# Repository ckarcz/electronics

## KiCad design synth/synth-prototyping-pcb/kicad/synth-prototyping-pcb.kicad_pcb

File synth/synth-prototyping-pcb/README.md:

# Prototyping PCB for Eurorack

Basic breadboard style pcb with Eurorack power connector.

# PCB

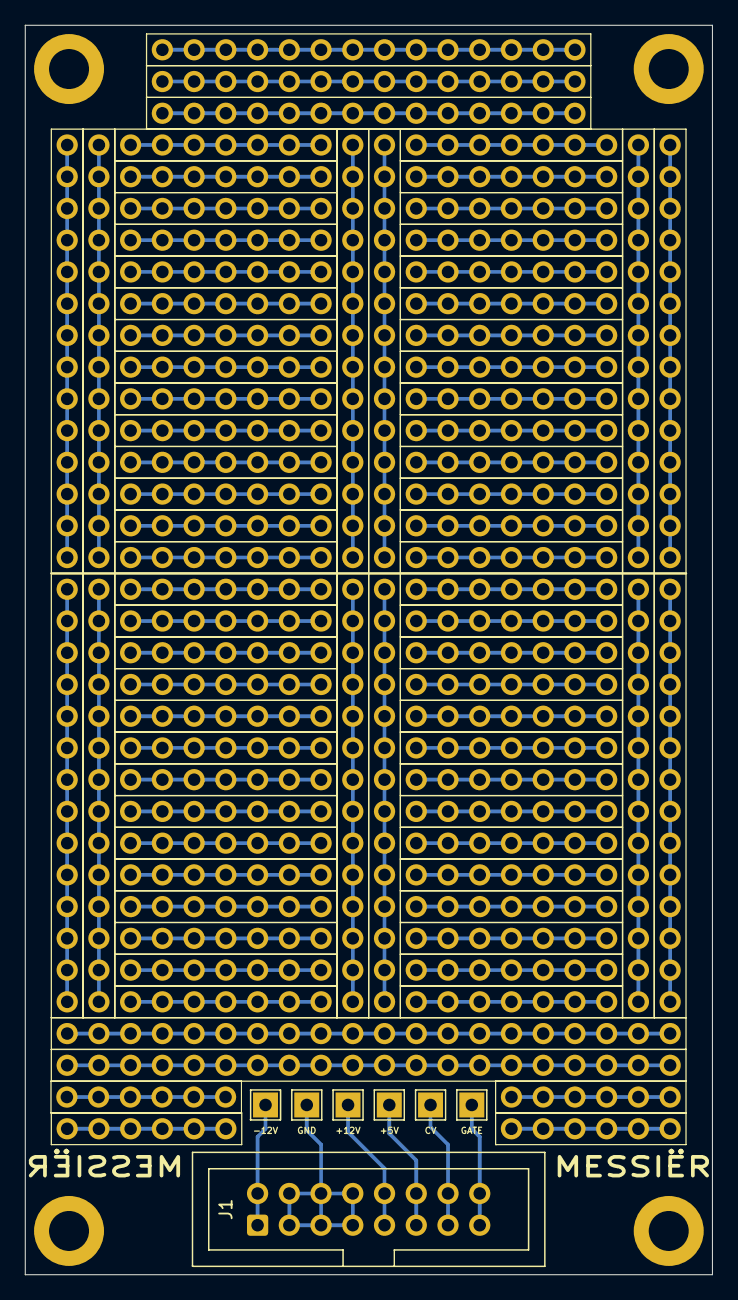
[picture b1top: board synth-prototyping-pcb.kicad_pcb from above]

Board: 2 copper layers, 55.0 x 100.0 mm, 11 parts (0 on the bottom side), 6 nets.

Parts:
J1: Conn_02x16_Odd_Even; IDC-Header_2x08_P2.54mm_Vertical
M1, M1#2, M1#3, M1#4: MountingHole_3.2mm_M3_DIN965_Pad
TP1: +5V; TestPoint_THTPad_2.0x2.0mm_Drill1.0mm
TP2: GND; TestPoint_THTPad_2.0x2.0mm_Drill1.0mm
TP3: +12V; TestPoint_THTPad_2.0x2.0mm_Drill1.0mm
TP4: -12V; TestPoint_THTPad_2.0x2.0mm_Drill1.0mm
TP5: CV; TestPoint_THTPad_2.0x2.0mm_Drill1.0mm
TP6: GATE; TestPoint_THTPad_2.0x2.0mm_Drill1.0mm

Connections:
+5V: J1.11, J1.12, TP1.1
+12V: J1.9, J1.10, TP3.1
-12V: J1.1, J1.2, TP4.1
CV: J1.13, J1.14, TP5.1
GATE: J1.15, J1.16, TP6.1
GND: J1.3, J1.4, J1.5, J1.6, J1.7, J1.8, TP2.1

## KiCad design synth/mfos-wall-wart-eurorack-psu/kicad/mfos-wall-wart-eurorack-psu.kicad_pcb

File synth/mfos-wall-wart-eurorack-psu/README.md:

# MFOS Wall Wart PSU For Eurorack

Basic wall wart design but with eurorack power rails + connector. Sub 100mm desing for cheap PCB manufactoring.

[Based on Ray Wilson's PSU circuit](https://shop.musicfromouterspace.com/cart/mfos-wall-wart-bipolar-power-supply).

# Schematic

# PCB

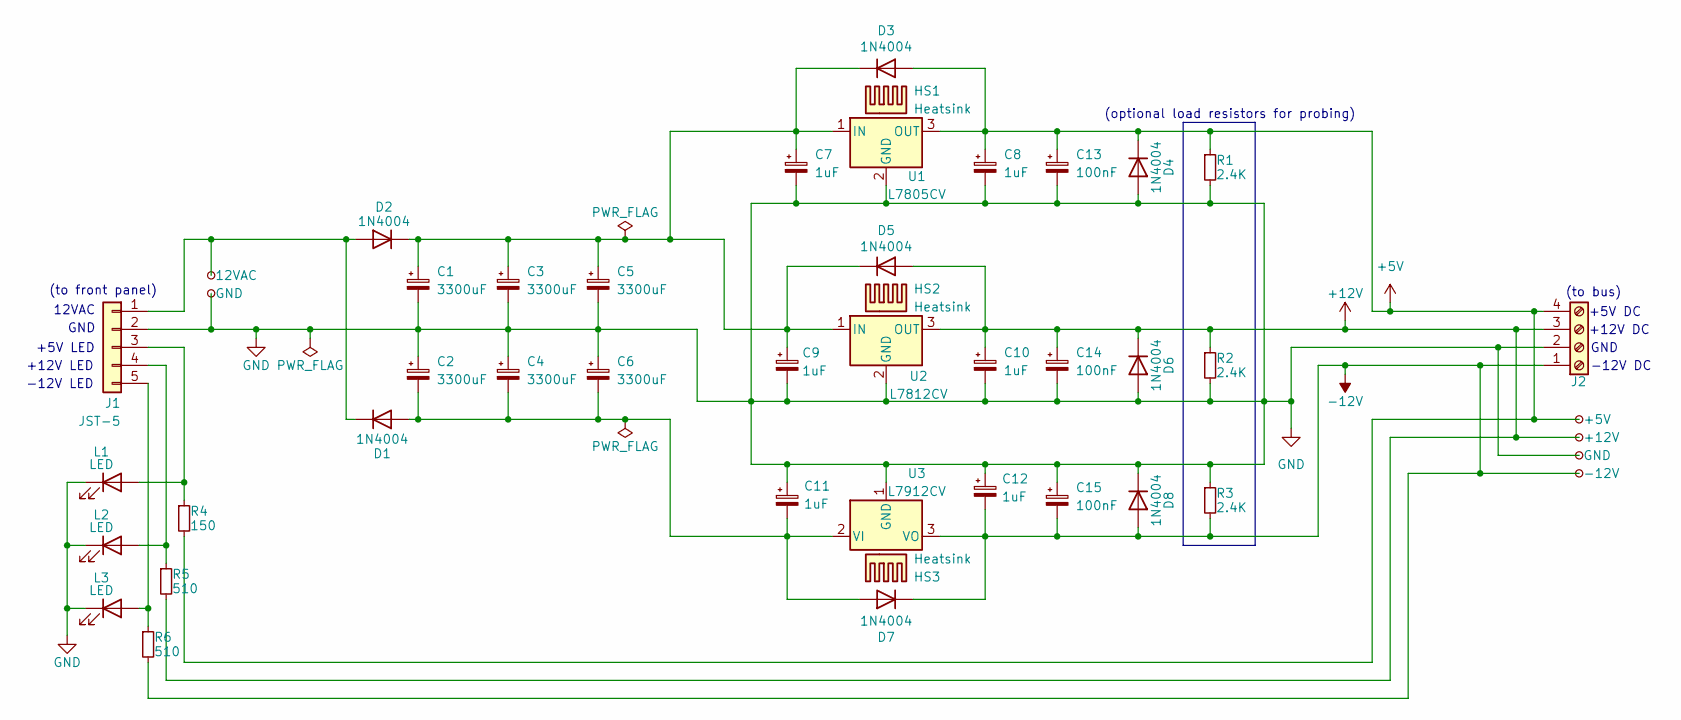
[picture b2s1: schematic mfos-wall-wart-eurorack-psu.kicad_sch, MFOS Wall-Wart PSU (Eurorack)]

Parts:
C1, C2, C3, C4, C5, C6: 3300uF; CP_Radial_D18.0mm_P7.50mm
C7, C8, C9, C10, C11, C12: 1uF; CP_Radial_Tantal_D5.0mm_P2.50mm
C13, C14, C15: 100nF; C_Disc_D3.0mm_W2.0mm_P2.50mm
D1, D2, D3, D4, D5, D6, D7, D8: 1N4004; D_DO-41_SOD81_P10.16mm_Horizontal
HS1, HS2, HS3: Heatsink; Heatsink_Tayda_16.50x16.50
J1: JST-5; JST_EH_B5B-EH-A_1x05_P2.50mm_Vertical
J2: TERMINAL-4; TerminalBlock_Phoenix_MKDS-1,5-4-5.08_1x04_P5.08mm_Horizont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
L1, L2, L3: LED; LED_D3.0mm
R1, R2, R3: 2.4K; R_Axial_DIN0207_L6.3mm_D2.5mm_P10.16mm_Horizontal
R4: 150; R_Axial_DIN0207_L6.3mm_D2.5mm_P10.16mm_Horizontal
R5, R6: 510; R_Axial_DIN0207_L6.3mm_D2.5mm_P10.16mm_Horizontal
TP1: 12VAC; TestPoint_THTPad_D1.5mm_Drill0.7mm
TP2, TP5: GND; TestPoint_THTPad_D1.5mm_Drill0.7mm
TP3: +5V; TestPoint_THTPad_D1.5mm_Drill0.7mm
TP4: +12V; TestPoint_THTPad_D1.5mm_Drill0.7mm
TP6: -12V; TestPoint_THTPad_D1.5mm_Drill0.7mm
U1: L7805CV; TO-220-3_Vertical
U2: L7812CV; TO-220-3_Vertical
U3: L7912CV; TO-220-3_Vertical

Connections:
12VAC: D1.1 (K), D2.2 (A), J1.1, TP1.1
+5V: C8.1, C13.1, D3.2 (A), D4.1 (K), J2.4, R1.1, R4.2, TP3.1, U1.3 (OUT)
+5V-LED: J1.3, L1.2 (A), R4.1
+12V: C10.1, C14.1, D5.2 (A), D6.1 (K), J2.3, R2.1, R5.2, TP4.1, U2.3 (OUT)
+12V-LED: J1.4, L2.2 (A), R5.1
-12V: C12.2, C15.2, D7.1 (K), D8.2 (A), J2.1, R3.2, R6.2, TP6.1, U3.3 (VO)
-12V-LED: J1.5, L3.2 (A), R6.1
GND: C1.2, C2.1, C3.2, C4.1, C5.2, C6.1, C7.2, C8.2, C9.2, C10.2, C11.1, C12.1, C13.2, C14.2, C15.1, D4.2 (A), D6.2 (A), D8.1 (K), J1.2, J2.2, L1.1 (K), L2.1 (K), L3.1 (K), R1.2, R2.2, R3.1, TP2.1, TP5.1, U1.2 (GND), U2.2 (GND), U3.1 (GND)
unnamed: C2.2, C4.2, C6.2, C11.2, D1.2 (A), D7.2 (A), U3.2 (VI)
unnamed: C1.1, C3.1, C5.1, C7.1, C9.1, D2.1 (K), D3.1 (K), D5.1 (K), U1.1 (IN), U2.1 (IN)

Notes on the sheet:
+5V DC
(optional load resistors for probing)
GND
-12V LED
+12V LED
+5V LED
+12V DC
12VAC
-12V DC
(to bus)
(to front panel)

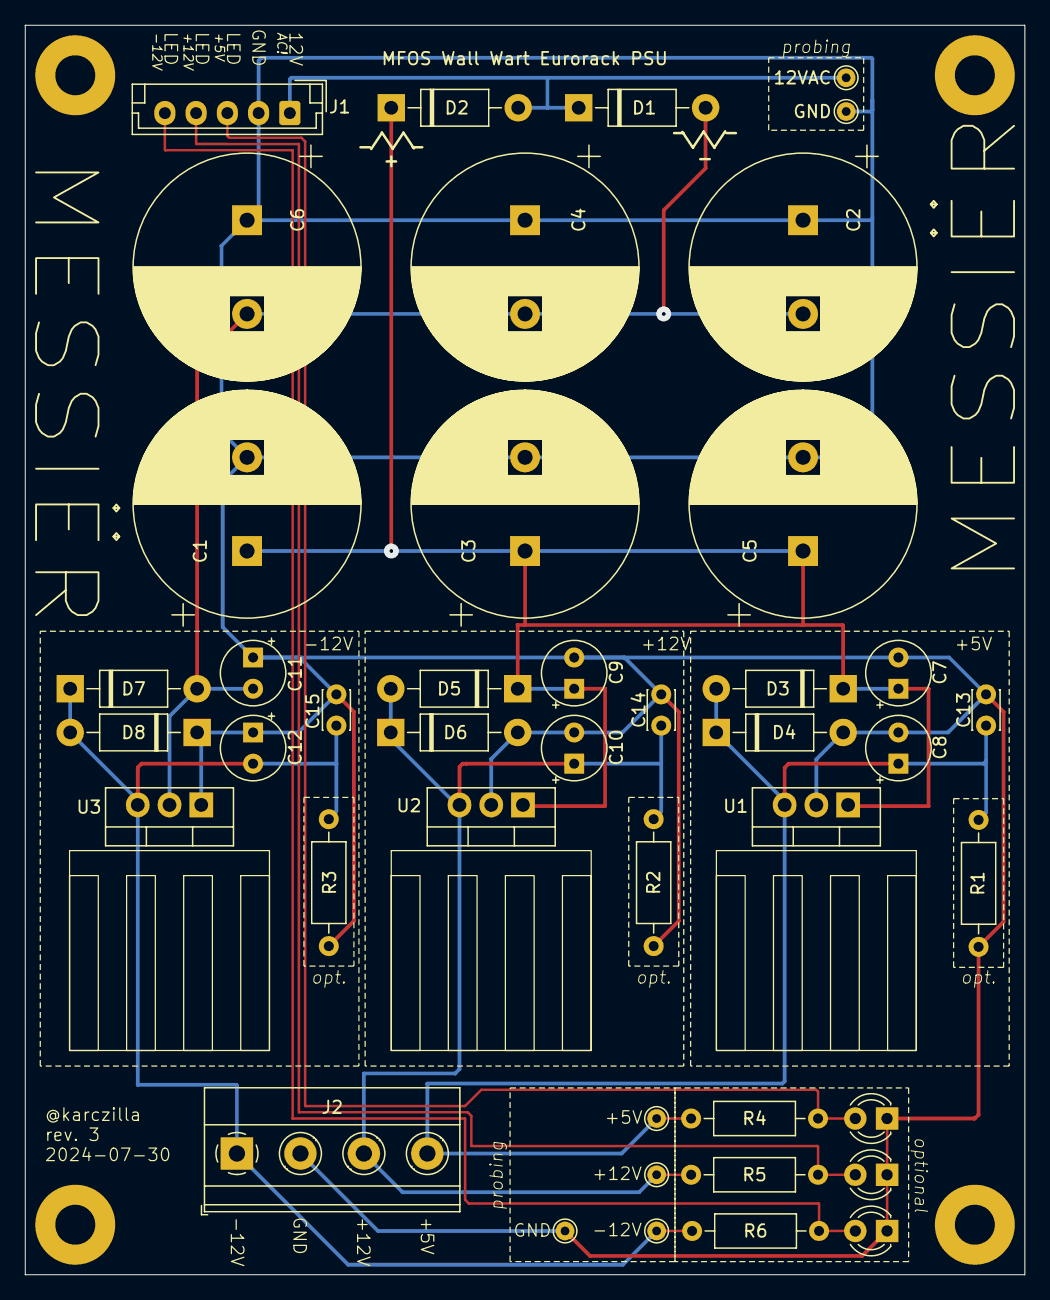
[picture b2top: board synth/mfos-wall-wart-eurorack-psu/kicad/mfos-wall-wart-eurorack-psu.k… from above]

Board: 2 copper layers, 80.0 x 100.0 mm, 50 parts (0 on the bottom side), 10 nets.

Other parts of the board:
M1, M2, M3, M4: MountingHole_3.2mm_M3_Pad

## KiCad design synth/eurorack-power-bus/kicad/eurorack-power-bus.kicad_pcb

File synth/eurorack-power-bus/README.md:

# Power Bus for Eurorack (Passive)

Basic passive power distribution bus for eurorack.

# Schematic

# PCB

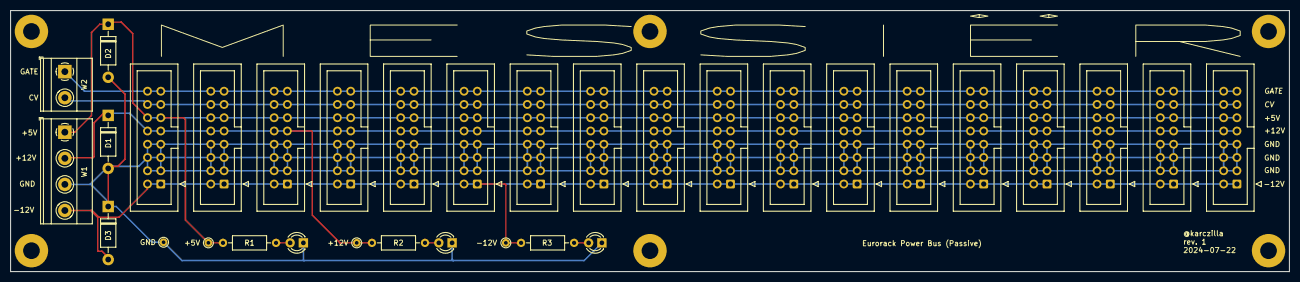
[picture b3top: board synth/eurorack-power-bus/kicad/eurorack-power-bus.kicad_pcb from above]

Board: 2 copper layers, 245.0 x 50.0 mm, 39 parts (0 on the bottom side), 9 nets.

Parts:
D1, D2, D3: D_Small; D_DO-41_SOD81_P10.16mm_Horizontal
J1, J2, J3, J4, J5, J6, J7, J8, J9, J10, J11, J12, J13, J14, J15, J16, J17, J18: IDC16; IDC-Header_2x08_P2.54mm_Vertical
L1, L2, L3: LED; LED_D3.0mm
M1, M2, M3, M3#2, M4, M4#2: MountingHole_3.2mm_M3_Pad
R1: 150; R_Axial_DIN0207_L6.3mm_D2.5mm_P10.16mm_Horizontal
R2, R3: 500; R_Axial_DIN0207_L6.3mm_D2.5mm_P10.16mm_Horizontal
TP1: +5V; TestPoint_THTPad_D1.5mm_Drill0.7mm
TP3: -12V; TestPoint_THTPad_D1.5mm_Drill0.7mm
TP4: GND; TestPoint_THTPad_D1.5mm_Drill0.7mm
TP{2: +12V; TestPoint_THTPad_D1.5mm_Drill0.7mm
W1: Screw_Terminal_01x04; TerminalBlock_Phoenix_MKDS-1,5-4_1x04_P5.00mm_Horizontal
W2: Screw_Terminal_01x02; TerminalBlock_Phoenix_MKDS-1,5-2_1x02_P5.00mm_Horizontal

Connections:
+5V: D2.1 (K), J1.11, J1.12, J2.11, J2.12, J3.11, J3.12, J4.11, J4.12, J5.11, J5.12, J6.11, J6.12, J7.11, J7.12, J8.11, J8.12, J9.11, J9.12, J10.11, J10.12, J11.11, J11.12, J12.11, J12.12, J13.11, J13.12, J14.11, J14.12, J15.11, J15.12, J16.11, J16.12, J17.11, J17.12, J18.11, J18.12, R1.1, TP1.1, W1.1
+12V: D1.1 (K), J1.9, J1.10, J2.9, J2.10, J3.9, J3.10, J4.9, J4.10, J5.9, J5.10, J6.9, J6.10, J7.9, J7.10, J8.9, J8.10, J9.9, J9.10, J10.9, J10.10, J11.9, J11.10, J12.9, J12.10, J13.9, J13.10, J14.9, J14.10, J15.9, J15.10, J16.9, J16.10, J17.9, J17.10, J18.9, J18.10, R2.1, TP{2.1, W1.2
-12V: D3.2 (A), J1.1, J1.2, J2.1, J2.2, J3.1, J3.2, J4.1, J4.2, J5.1, J5.2, J6.1, J6.2, J7.1, J7.2, J8.1, J8.2, J9.1, J9.2, J10.1, J10.2, J11.1, J11.2, J12.1, J12.2, J13.1, J13.2, J14.1, J14.2, J15.1, J15.2, J16.1, J16.2, J17.1, J17.2, J18.1, J18.2, R3.1, TP3.1, W1.4
CV: J1.13, J1.14, J2.13, J2.14, J3.13, J3.14, J4.13, J4.14, J5.13, J5.14, J6.13, J6.14, J7.13, J7.14, J8.13, J8.14, J9.13, J9.14, J10.13, J10.14, J11.13, J11.14, J12.13, J12.14, J13.13, J13.14, J14.13, J14.14, J15.13, J15.14, J16.13, J16.14, J17.13, J17.14, J18.13, J18.14, W2.2
GATE: J1.15, J1.16, J2.15, J2.16, J3.15, J3.16, J4.15, J4.16, J5.15, J5.16, J6.15, J6.16, J7.15, J7.16, J8.15, J8.16, J9.15, J9.16, J10.15, J10.16, J11.15, J11.16, J12.15, J12.16, J13.15, J13.16, J14.15, J14.16, J15.15, J15.16, J16.15, J16.16, J17.15, J17.16, J18.15, J18.16, W2.1
GND: D1.2 (A), D2.2 (A), D3.1 (K), J1.3, J1.4, J1.5, J1.6, J1.7, J1.8, J2.3, J2.4, J2.5, J2.6, J2.7, J2.8, J3.3, J3.4, J3.5, J3.6, J3.7, J3.8, J4.3, J4.4, J4.5, J4.6, J4.7, J4.8, J5.3, J5.4, J5.5, J5.6, J5.7, J5.8, J6.3, J6.4, J6.5, J6.6, J6.7, J6.8, J7.3, J7.4, J7.5, J7.6, J7.7, J7.8, J8.3, J8.4, J8.5, J8.6, J8.7, J8.8, J9.3, J9.4, J9.5, J9.6, J9.7, J9.8, J10.3, J10.4, J10.5, J10.6, J10.7, J10.8, J11.3, J11.4, J11.5, J11.6, J11.7, J11.8, J12.3, J12.4, J12.5, J12.6, J12.7, J12.8, J13.3, J13.4, J13.5, J13.6, J13.7, J13.8, J14.3, J14.4, J14.5, J14.6, J14.7, J14.8, J15.3, J15.4, J15.5, J15.6, J15.7, J15.8, J16.3, J16.4, J16.5, J16.6, J16.7, J16.8, J17.3, J17.4, J17.5, J17.6, J17.7, J17.8, J18.3, J18.4, J18.5, J18.6, J18.7, J18.8, L1.1 (K), L2.1 (K), L3.1 (K), TP4.1, W1.3
unnamed: L1.2 (A), R1.2
unnamed: L2.2 (A), R2.2
unnamed: L3.2 (A), R3.2

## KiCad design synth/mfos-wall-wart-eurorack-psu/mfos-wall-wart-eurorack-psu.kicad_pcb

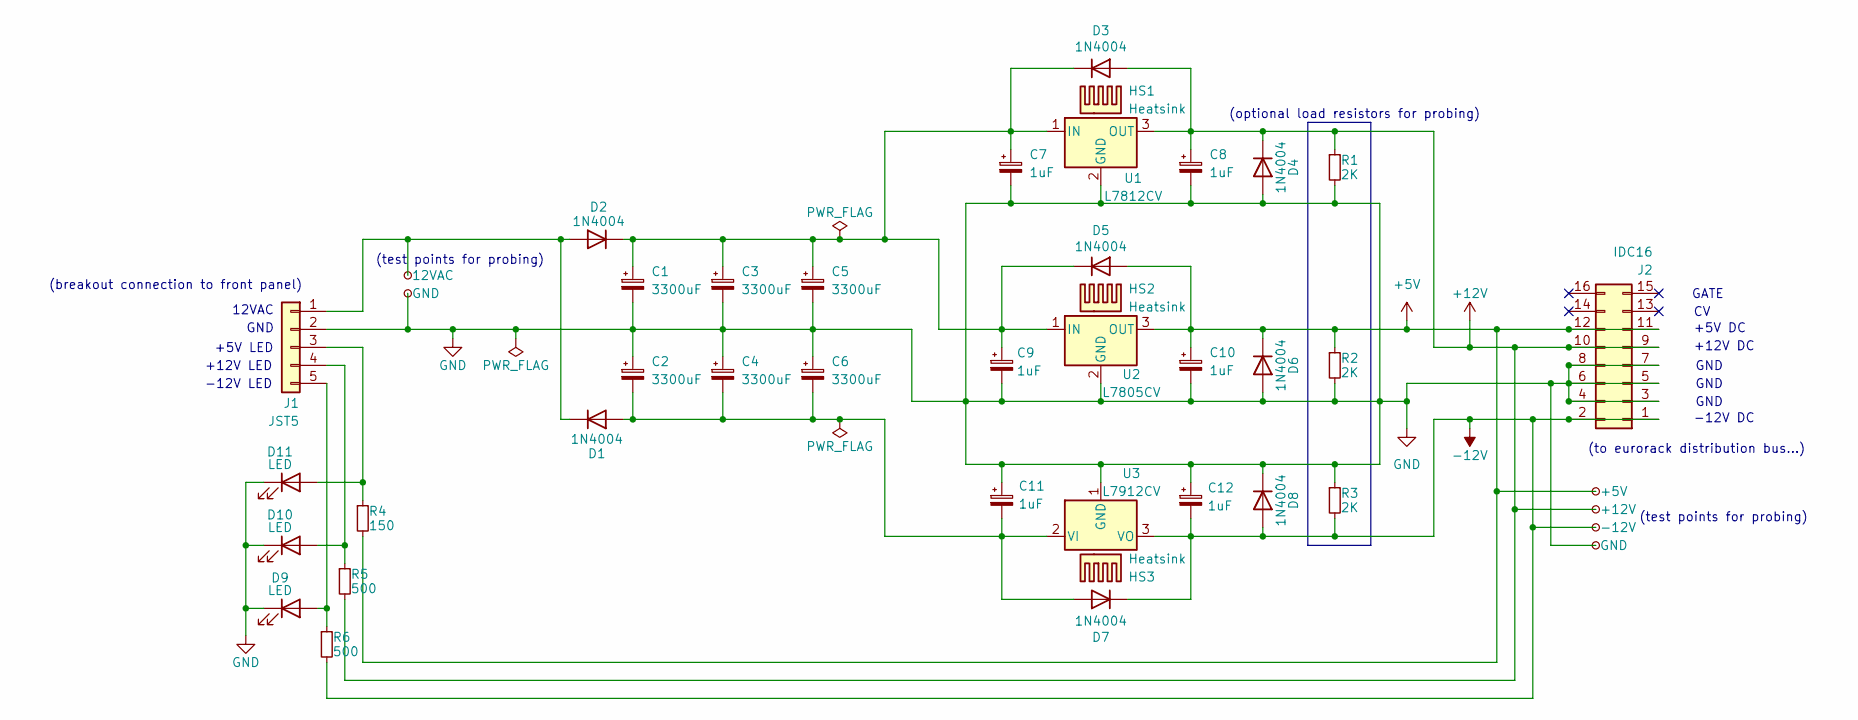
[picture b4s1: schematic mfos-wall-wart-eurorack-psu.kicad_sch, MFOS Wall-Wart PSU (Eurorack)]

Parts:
C1, C2, C3, C4, C5, C6: 3300uF; CP_Radial_D18.0mm_P7.50mm
C7, C8, C9, C10, C11, C12: 1uF; CP_Radial_Tantal_D5.0mm_P2.50mm
D1, D2, D3, D4, D5, D6, D7, D8: 1N4004; D_DO-41_SOD81_P10.16mm_Horizontal
D9, D10, D11: LED; LED_D3.0mm
HS1, HS2, HS3: Heatsink; Heatsink_Tayda_16.50x16.50
J1: JST5; JST_EH_B5B-EH-A_1x05_P2.50mm_Vertical
J2: IDC16; IDC-Header_2x08_P2.54mm_Vertical
R1, R2, R3: 2K; R_Axial_DIN0207_L6.3mm_D2.5mm_P10.16mm_Horizontal
R4: 150; R_Axial_DIN0207_L6.3mm_D2.5mm_P10.16mm_Horizontal
R5, R6: 500; R_Axial_DIN0207_L6.3mm_D2.5mm_P10.16mm_Horizontal
TP1: 12VAC; TestPoint_THTPad_D1.5mm_Drill0.7mm
TP2, TP6: GND; TestPoint_THTPad_D1.5mm_Drill0.7mm
TP3: +5V; TestPoint_THTPad_D1.5mm_Drill0.7mm
TP4: +12V; TestPoint_THTPad_D1.5mm_Drill0.7mm
TP5: -12V; TestPoint_THTPad_D1.5mm_Drill0.7mm
U1: L7812CV; TO-220-3_Vertical
U2: L7805CV; TO-220-3_Vertical
U3: L7912CV; TO-220-3_Vertical

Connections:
+5V: C10.1, D5.2 (A), D6.1 (K), J2.11, J2.12, R2.1, R4.2, TP3.1, U2.3 (OUT)
+12V: C8.1, D3.2 (A), D4.1 (K), J2.9, J2.10, R1.1, R5.2, TP4.1, U1.3 (OUT)
-12V: C12.2, D7.1 (K), D8.2 (A), J2.1, J2.2, R3.2, R6.2, TP5.1, U3.3 (VO)
GND: C1.2, C2.1, C3.2, C4.1, C5.2, C6.1, C7.2, C8.2, C9.2, C10.2, C11.1, C12.1, D4.2 (A), D6.2 (A), D8.1 (K), D9.1 (K), D10.1 (K), D11.1 (K), J1.2, J2.3, J2.4, J2.5, J2.6, J2.7, J2.8, R1.2, R2.2, R3.1, TP2.1, TP6.1, U1.2 (GND), U2.2 (GND), U3.1 (GND)
unnamed: C2.2, C4.2, C6.2, C11.2, D1.2 (A), D7.2 (A), U3.2 (VI)
unnamed: D1.1 (K), D2.2 (A), J1.1, TP1.1
unnamed: C1.1, C3.1, C5.1, C7.1, C9.1, D2.1 (K), D3.1 (K), D5.1 (K), U1.1 (IN), U2.1 (IN)
unnamed: D9.2 (A), J1.5, R6.1
unnamed: D10.2 (A), J1.4, R5.1
unnamed: D11.2 (A), J1.3, R4.1

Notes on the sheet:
+5V DC
(optional load resistors for probing)
GND
-12V LED
+12V LED
(test points for probing)
+5V LED
+12V DC
12VAC
GATE
-12V DC
(to eurorack distribution bus...)
(breakout connection to front panel)

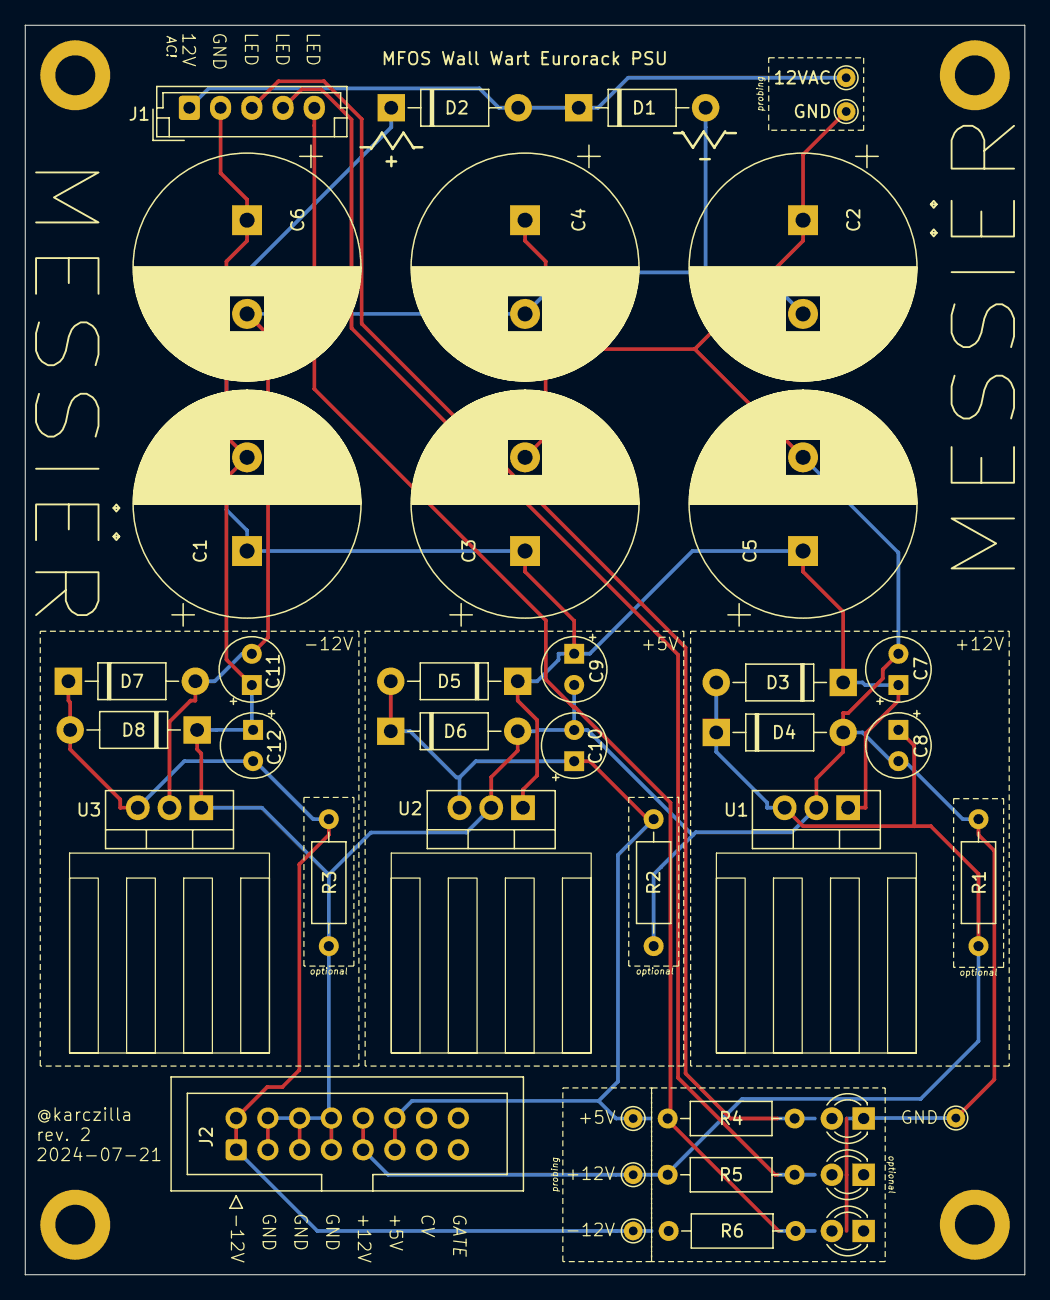
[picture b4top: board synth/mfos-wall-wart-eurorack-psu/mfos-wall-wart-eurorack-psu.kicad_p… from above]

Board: 2 copper layers, 80.0 x 100.0 mm, 47 parts (0 on the bottom side), 10 nets.

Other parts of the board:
M1, M2, M3, M4: MountingHole_3.2mm_M3_DIN965_Pad

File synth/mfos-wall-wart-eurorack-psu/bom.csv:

"Reference","Value","Description","Qty"
"C1,C2,C3,C4,C5,C6","3300uF","3300UF 50V RADIAL ELECTROLYTIC CAPACITOR 18X40MM ","6"
"C7,C8,C9,C10,C11,C12","1uF","1UF 50V RADIAL ELECTROLYTIC CAPACITOR 5X11MM ","6"
"D1,D2,D3,D4,D5,D6,D7,D8","1N4004","400V 1A General Purpose Rectifier Diode, DO-41","8"
"D9,D10,D11","LED","3mm LED","3"
"HS1,HS2,HS3","Heatsink","HEATSINK TO-220 4 FINS ALUMINIUM 17mmLx17mmWx26mmH","3"
"J1","JST5","5 PINS JST XH-2.54 FEMALE CONNECTOR","1"
"J2","IDC16","IDC 2x8","1"
"R1,R2,R3","2K","2K OHM 1/2W 1% METAL FILM RESISTOR","3"
"R4","150","Resistor, small symbol","1"
"R5,R6","500","Resistor, small symbol","2"
"TP1","12VAC","Test Point","1"
"TP2,TP6","GND","Test Point","2"
"TP3","+5V","Test Point","1"
"TP4","+12V","Test Point","1"
"TP5","-12V","Test Point","1"
"U1","L7812CV","L7812 VOLTAGE REGULATOR IC +12V 1.5A ","1"
"U2","L7805CV","L7805 VOLTAGE REGULATOR IC +5V 1.5A ","1"
"U3","L7912CV","L7912 VOLTAGE REGULATOR IC -12V 1.5A ","1"

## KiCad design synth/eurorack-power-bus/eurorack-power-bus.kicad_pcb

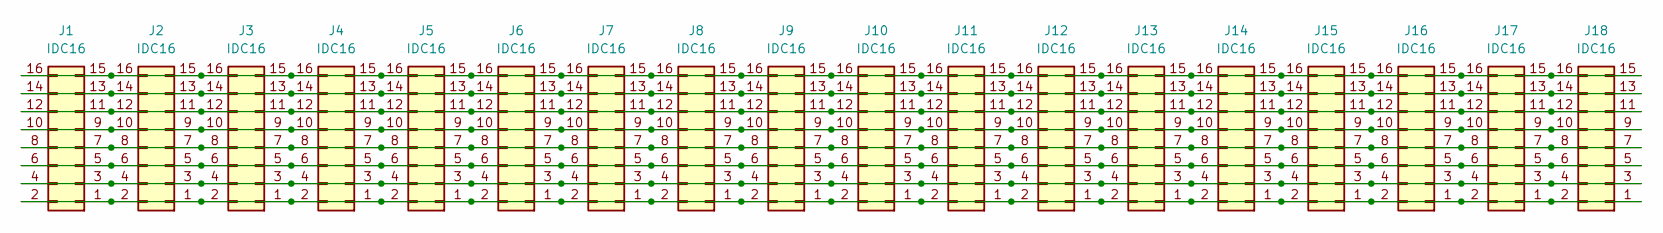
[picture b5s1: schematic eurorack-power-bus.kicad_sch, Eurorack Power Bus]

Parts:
J1, J2, J3, J4, J5, J6, J7, J8, J9, J10, J11, J12, J13, J14, J15, J16, J17, J18: IDC16; IDC-Header_2x08_P2.54mm_Vertical

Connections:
unnamed: J1.1, J1.2, J2.1, J2.2, J3.1, J3.2, J4.1, J4.2, J5.1, J5.2, J6.1, J6.2, J7.1, J7.2, J8.1, J8.2, J9.1, J9.2, J10.1, J10.2, J11.1, J11.2, J12.1, J12.2, J13.1, J13.2, J14.1, J14.2, J15.1, J15.2, J16.1, J16.2, J17.1, J17.2, J18.1, J18.2
unnamed: J1.3, J1.4, J2.3, J2.4, J3.3, J3.4, J4.3, J4.4, J5.3, J5.4, J6.3, J6.4, J7.3, J7.4, J8.3, J8.4, J9.3, J9.4, J10.3, J10.4, J11.3, J11.4, J12.3, J12.4, J13.3, J13.4, J14.3, J14.4, J15.3, J15.4, J16.3, J16.4, J17.3, J17.4, J18.3, J18.4
unnamed: J1.5, J1.6, J2.5, J2.6, J3.5, J3.6, J4.5, J4.6, J5.5, J5.6, J6.5, J6.6, J7.5, J7.6, J8.5, J8.6, J9.5, J9.6, J10.5, J10.6, J11.5, J11.6, J12.5, J12.6, J13.5, J13.6, J14.5, J14.6, J15.5, J15.6, J16.5, J16.6, J17.5, J17.6, J18.5, J18.6
unnamed: J1.7, J1.8, J2.7, J2.8, J3.7, J3.8, J4.7, J4.8, J5.7, J5.8, J6.7, J6.8, J7.7, J7.8, J8.7, J8.8, J9.7, J9.8, J10.7, J10.8, J11.7, J11.8, J12.7, J12.8, J13.7, J13.8, J14.7, J14.8, J15.7, J15.8, J16.7, J16.8, J17.7, J17.8, J18.7, J18.8
unnamed: J1.9, J1.10, J2.9, J2.10, J3.9, J3.10, J4.9, J4.10, J5.9, J5.10, J6.9, J6.10, J7.9, J7.10, J8.9, J8.10, J9.9, J9.10, J10.9, J10.10, J11.9, J11.10, J12.9, J12.10, J13.9, J13.10, J14.9, J14.10, J15.9, J15.10, J16.9, J16.10, J17.9, J17.10, J18.9, J18.10
unnamed: J1.11, J1.12, J2.11, J2.12, J3.11, J3.12, J4.11, J4.12, J5.11, J5.12, J6.11, J6.12, J7.11, J7.12, J8.11, J8.12, J9.11, J9.12, J10.11, J10.12, J11.11, J11.12, J12.11, J12.12, J13.11, J13.12, J14.11, J14.12, J15.11, J15.12, J16.11, J16.12, J17.11, J17.12, J18.11, J18.12
unnamed: J1.13, J1.14, J2.13, J2.14, J3.13, J3.14, J4.13, J4.14, J5.13, J5.14, J6.13, J6.14, J7.13, J7.14, J8.13, J8.14, J9.13, J9.14, J10.13, J10.14, J11.13, J11.14, J12.13, J12.14, J13.13, J13.14, J14.13, J14.14, J15.13, J15.14, J16.13, J16.14, J17.13, J17.14, J18.13, J18.14
unnamed: J1.15, J1.16, J2.15, J2.16, J3.15, J3.16, J4.15, J4.16, J5.15, J5.16, J6.15, J6.16, J7.15, J7.16, J8.15, J8.16, J9.15, J9.16, J10.15, J10.16, J11.15, J11.16, J12.15, J12.16, J13.15, J13.16, J14.15, J14.16, J15.15, J15.16, J16.15, J16.16, J17.15, J17.16, J18.15, J18.16

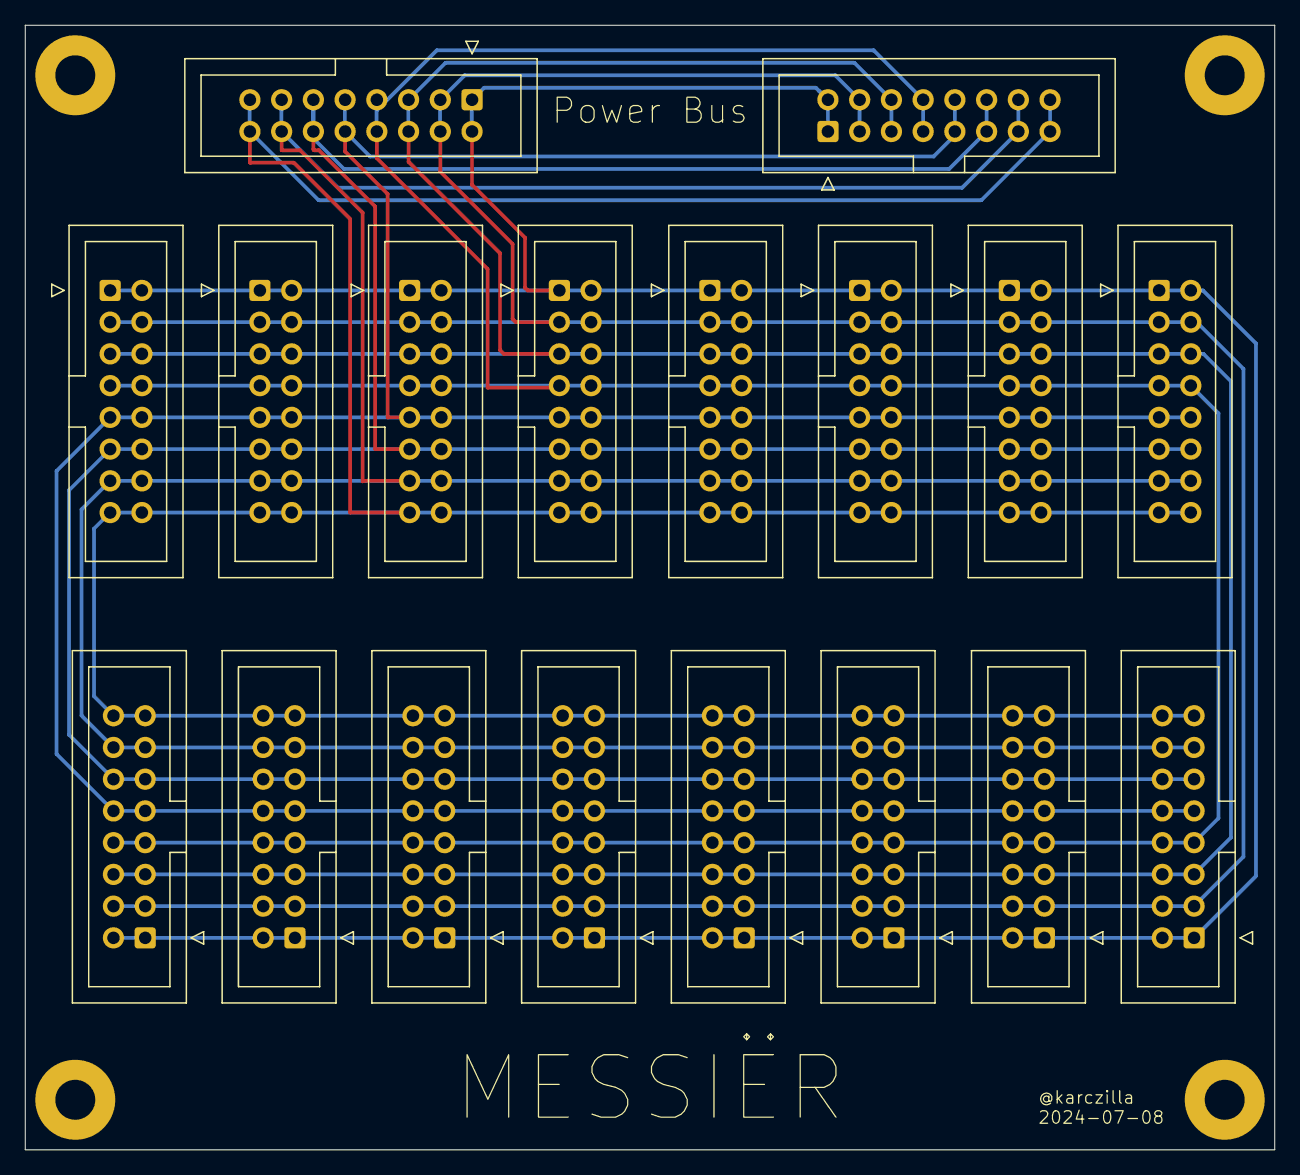
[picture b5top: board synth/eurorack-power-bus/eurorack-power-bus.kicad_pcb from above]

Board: 2 copper layers, 100.0 x 90.0 mm, 22 parts (0 on the bottom side), 8 nets.

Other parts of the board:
M1, M2, M3, M4: MountingHole_3.2mm_M3_Pad

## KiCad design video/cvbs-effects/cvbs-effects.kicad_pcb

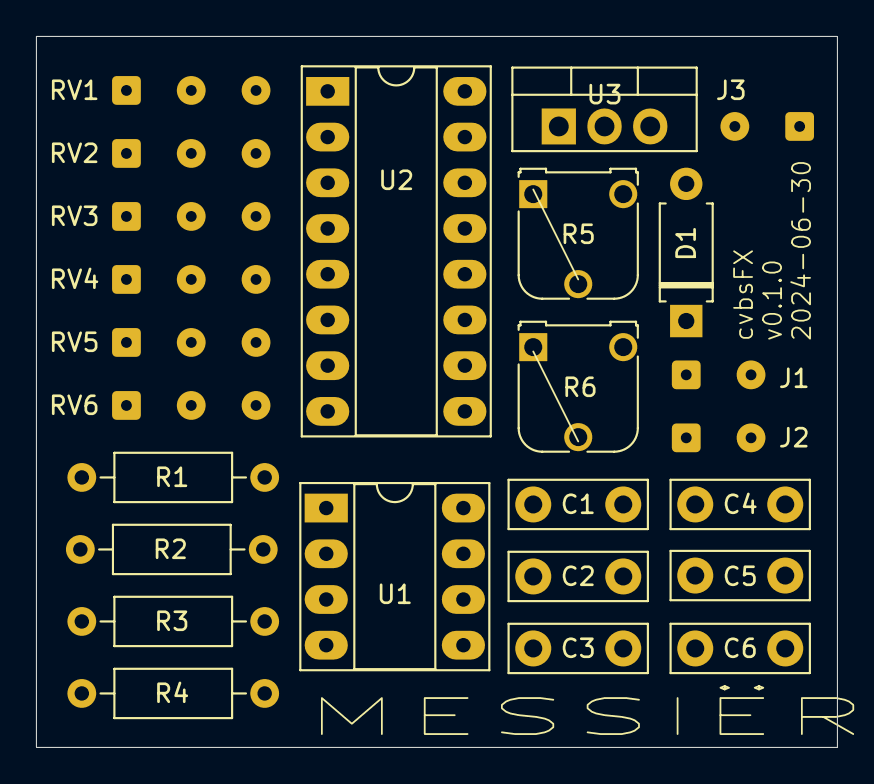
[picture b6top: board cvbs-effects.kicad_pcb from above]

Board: 2 copper layers, 44.5 x 39.5 mm, 25 parts (0 on the bottom side), 19 nets, no tracks yet.

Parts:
C1, C2, C3, C4, C6: 0.1u; C_Disc_D7.5mm_W2.5mm_P5.00mm
C5: 0.22u; C_Disc_D7.5mm_W2.5mm_P5.00mm
D1: 1N4007; D_A-405_P7.62mm_Horizontal
J1: CVBS_IN; SolderWire-0.1sqmm_1x02_P3.6mm_D0.4mm_OD1mm
J2: CVBS_OUT; SolderWire-0.1sqmm_1x02_P3.6mm_D0.4mm_OD1mm
J3: DC JACK; SolderWire-0.1sqmm_1x02_P3.6mm_D0.4mm_OD1mm
R1: 75; R_Axial_DIN0207_L6.3mm_D2.5mm_P10.16mm_Horizontal
R2: 680k; R_Axial_DIN0207_L6.3mm_D2.5mm_P10.16mm_Horizontal
R3, R4: 1k; R_Axial_DIN0207_L6.3mm_D2.5mm_P10.16mm_Horizontal
R5, R6: R_Trim; Potentiometer_Runtron_RM-065_Vertical
RV1, RV2, RV3, RV4: 10k; SolderWire-0.1sqmm_1x03_P3.6mm_D0.4mm_OD1mm
RV5, RV6: 1k; SolderWire-0.1sqmm_1x03_P3.6mm_D0.4mm_OD1mm
U1: LM1881; DIP-8_W7.62mm_Socket_LongPads
U2: LM339; DIP-16_W7.62mm_Socket_LongPads
U3: LM7805; TO-220-3_Vertical

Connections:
+5V: C3.2, C4.2, C6.1, R3.1, R4.1, R6.1, U1.8 (VCC), U2.3 (V+), U3.1 (VI)
GND: C2.2, C3.1, C4.1, C5.2, C6.2, J1.2 (Ext), J2.2 (Ext), J3.2, R1.2, R2.2, R5.2, RV5.1, RV6.1, U1.4 (GND), U2.12 (V-), U3.2 (GND)
unnamed: D1.2 (A), J3.1
unnamed: C5.1, D1.1 (K), U3.3 (VO)
unnamed: C1.2, J1.1 (In), R1.1
unnamed: J2.1 (In), RV5.2, RV6.2, U1.1 (CSYNC)
unnamed: R3.2, RV5.3, U2.1, U2.2
unnamed: R4.2, RV6.3, U2.13, U2.14
unnamed: R5.1, RV4.1
unnamed: R6.2, RV1.3
unnamed: RV1.1, RV2.3
unnamed: RV2.1, RV3.3
unnamed: RV3.1, RV4.3
unnamed: C2.1, R2.1, U1.6 (INT)
unnamed: C1.1, U1.2 (VIDEO), U2.4 (-), U2.7 (+), U2.9 (+), U2.10 (-)
unnamed: RV1.2, U2.5 (+)
unnamed: RV2.2, U2.6 (-)
unnamed: RV3.2, U2.11 (+)
unnamed: RV4.2, U2.8 (-)

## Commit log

2024-07-08 git ignores
2024-07-08 eurorack power bus sch + pcb
2024-07-09 tracing
2024-07-09 gerbers
2024-07-12 cvbs decomposer wip
2024-07-12 fix 4538 terminations
2024-07-20 add red stripe
2024-07-21 psu bom
2024-07-21 rev 2
2024-07-22 ver2
2024-07-22 rev2
2024-07-22 rev2 gerbers
2024-07-23 revisions
2024-07-23 fixes
2024-07-25 pcb png
2024-07-25 bus models
2024-07-25 add edging to SCAD
2024-07-30 rev3
2024-07-31 prototyping board
2024-07-31 prototyping board readme
2024-07-31 improve split breadboard line
